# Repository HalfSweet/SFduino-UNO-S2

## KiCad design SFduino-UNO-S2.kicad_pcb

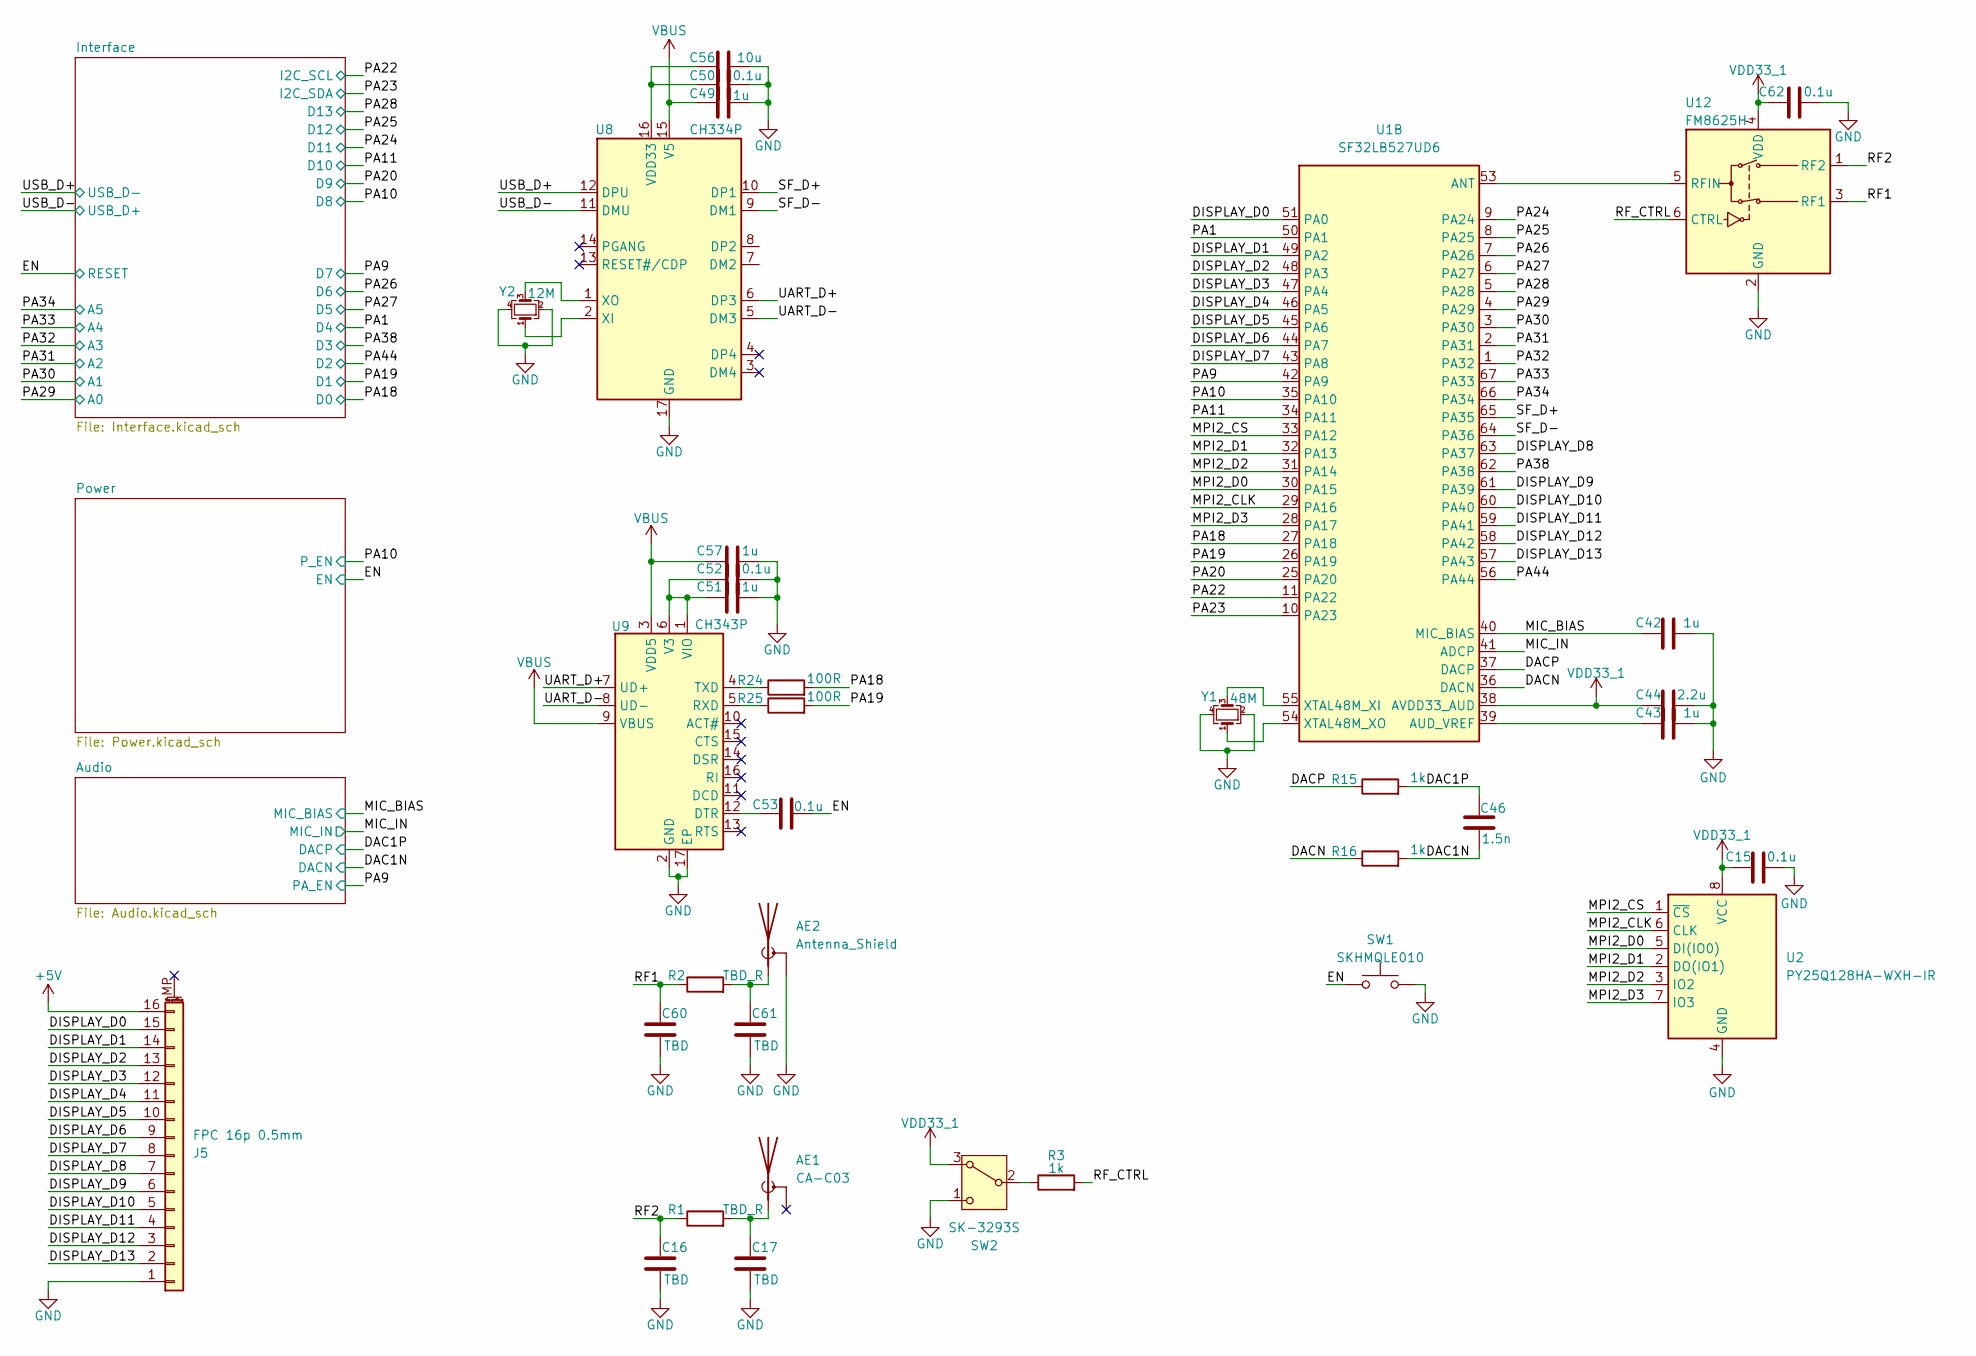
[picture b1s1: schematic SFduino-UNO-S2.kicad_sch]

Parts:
AE1: CA-C03
AE2: Antenna_Shield; U.FL_Molex_MCRF_73412-0110_Vertical
C15, C50, C52, C53, C62: 0.1u; C_0402_1005Metric
C16, C17, C60, C61: TBD; C_0402_1005Metric
C42, C43, C49, C51, C57: 1u; C_0402_1005Metric
C44: 2.2u; C_0402_1005Metric
C46: 1.5n; C_0402_1005Metric
C56: 10u; C_0402_1005Metric
J5: FPC 16p 0.5mm; Hirose_FH12-16S-0.5SH_1x16-1MP_P0.50mm_Horizontal
R1, R2: TBD_R; R_0402_1005Metric
R3, R15, R16: 1k; R_0402_1005Metric
R24, R25: 100R; R_0402_1005Metric
SW1: SKHMQLE010; KEY-SMD_4P-L6.2-W6.5-P4.50-LS8.0_SKHMXX
SW2: SK-3293S; SW-SMD_SK-3293S_mini_7P
U1: SF32LB527UD6; ArtInChip_QFN-68-1EP_7x7mm_P0.35mm_EP5.49x5.49mm
U2: PY25Q128HA-WXH-IR; WSON-8-1EP_6x5mm_P1.27mm_EP3.4x4.3mm
U8: CH334P; QFN-16-1EP_3x3mm_P0.5mm_EP1.7x1.7mm
U9: CH343P; QFN-16-1EP_3x3mm_P0.5mm_EP1.7x1.7mm
U12: FM8625H; Infineon_PG-TSNP-6-10_0.7x1.1mm_0.7x1.1mm_P0.4mm
Y1: 48M; Crystal_SMD_2016-4Pin_2.0x1.6mm
Y2: 12M; Crystal_SMD_2520-4Pin_2.5x2.0mm

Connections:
+5V: J5.16; also elsewhere on the board
/DAC1N: C46.2, R16.2; also elsewhere on the board
/DAC1P: C46.1, R15.2; also elsewhere on the board
/DACN: R16.1, U1.36 (DACN)
/DACP: R15.1, U1.37 (DACP)
/DISPLAY_D0: J5.15, U1.51 (PA0)
/DISPLAY_D1: J5.14, U1.49 (PA2)
/DISPLAY_D2: J5.13, U1.48 (PA3)
/DISPLAY_D3: J5.12, U1.47 (PA4)
/DISPLAY_D4: J5.11, U1.46 (PA5)
/DISPLAY_D5: J5.10, U1.45 (PA6)
/DISPLAY_D6: J5.9, U1.44 (PA7)
/DISPLAY_D7: J5.8, U1.43 (PA8)
/DISPLAY_D8: J5.7, U1.63 (PA37)
/DISPLAY_D9: J5.6, U1.61 (PA39)
/DISPLAY_D10: J5.5, U1.60 (PA40)
/DISPLAY_D11: J5.4, U1.59 (PA41)
/DISPLAY_D12: J5.3, U1.58 (PA42)
/DISPLAY_D13: J5.2, U1.57 (PA43)
/EN: C53.2, SW1.1; also elsewhere on the board
/MIC_BIAS: C42.1, U1.40 (MIC_BIAS); also elsewhere on the board
/MIC_IN: U1.41 (ADCP); also elsewhere on the board
/MPI2_CLK: U1.29 (PA16), U2.6 (CLK)
/MPI2_CS: U1.33 (PA12), U2.1 (~CS)
/MPI2_D0: U1.30 (PA15), U2.5 (DI(IO0))
/MPI2_D1: U1.32 (PA13), U2.2 (DO(IO1))
/MPI2_D2: U1.31 (PA14), U2.3 (IO2)
/MPI2_D3: U1.28 (PA17), U2.7 (IO3)
/PA1: U1.50 (PA1); also elsewhere on the board
/PA9: U1.42 (PA9); also elsewhere on the board
/PA10: U1.35 (PA10); also elsewhere on the board
/PA11: U1.34 (PA11); also elsewhere on the board
/PA18: R24.2, U1.27 (PA18); also elsewhere on the board
/PA19: R25.2, U1.26 (PA19); also elsewhere on the board
/PA20: U1.25 (PA20); also elsewhere on the board
/PA22: U1.11 (PA22); also elsewhere on the board
/PA23: U1.10 (PA23); also elsewhere on the board
/PA24: U1.9 (PA24); also elsewhere on the board
/PA25: U1.8 (PA25); also elsewhere on the board
/PA26: U1.7 (PA26); also elsewhere on the board
/PA27: U1.6 (PA27); also elsewhere on the board
/PA28: U1.5 (PA28); also elsewhere on the board
/PA29: U1.4 (PA29); also elsewhere on the board
/PA30: U1.3 (PA30); also elsewhere on the board
/PA31: U1.2 (PA31); also elsewhere on the board
/PA32: U1.1 (PA32); also elsewhere on the board
/PA33: U1.67 (PA33); also elsewhere on the board
/PA34: U1.66 (PA34); also elsewhere on the board
/PA38: U1.62 (PA38); also elsewhere on the board
/PA44: U1.56 (PA44); also elsewhere on the board
/RF1: C60.1, R2.1, U12.3 (RF1)
/RF2: C16.1, R1.1, U12.1 (RF2)
/RF_CTRL: R3.2, U12.6 (CTRL)
/SF_D+: U1.65 (PA35), U8.10 (DP1)
/SF_D-: U1.64 (PA36), U8.9 (DM1)
/UART_D+: U8.6 (DP3), U9.7 (UD+)
/UART_D-: U8.5 (DM3), U9.8 (UD-)
/USB_D+: U8.12 (DPU); also elsewhere on the board
/USB_D-: U8.11 (DMU); also elsewhere on the board
GND: AE2.2 (Shield), C15.2, C16.2, C17.2, C42.2, C43.2, C44.2, C49.2, C50.2, C51.2, C52.2, C56.2, C57.2, C60.2, C61.2, C62.2, J5.1, SW1.2, SW2.1 (C), U2.4 (GND), U8.17 (GND), U9.2 (GND), U9.17 (EP), U12.2 (GND), Y1.2, Y1.4, Y2.2, Y2.4; also elsewhere on the board
unnamed: AE1.1 (A), C17.1, R1.2
unnamed: AE2.1 (A), C61.1, R2.2
unnamed: R3.1, SW2.2 (B)
unnamed: C43.1, U1.39 (AUD_VREF)
unnamed: U1.55 (XTAL48M_XI), Y1.3
unnamed: U1.54 (XTAL48M_XO), Y1.1
unnamed: C50.1, C56.1, U8.16 (VDD33)
unnamed: U8.2 (XI), Y2.1
unnamed: U8.1 (XO), Y2.3
unnamed: C53.1, U9.12 (DTR)
unnamed: R25.1, U9.5 (RXD)
unnamed: R24.1, U9.4 (TXD)
unnamed: C51.1, C52.1, U9.1 (VIO), U9.6 (V3)
unnamed: U1.53 (ANT), U12.5 (RFIN)
VBUS: C49.1, C57.1, U8.15 (V5), U9.3 (VDD5), U9.9 (VBUS); also elsewhere on the board
VDD33_1: C15.1, C44.1, C62.1, SW2.3 (A), U1.38 (AVDD33_AUD), U2.8 (VCC), U12.4 (VDD); also elsewhere on the board

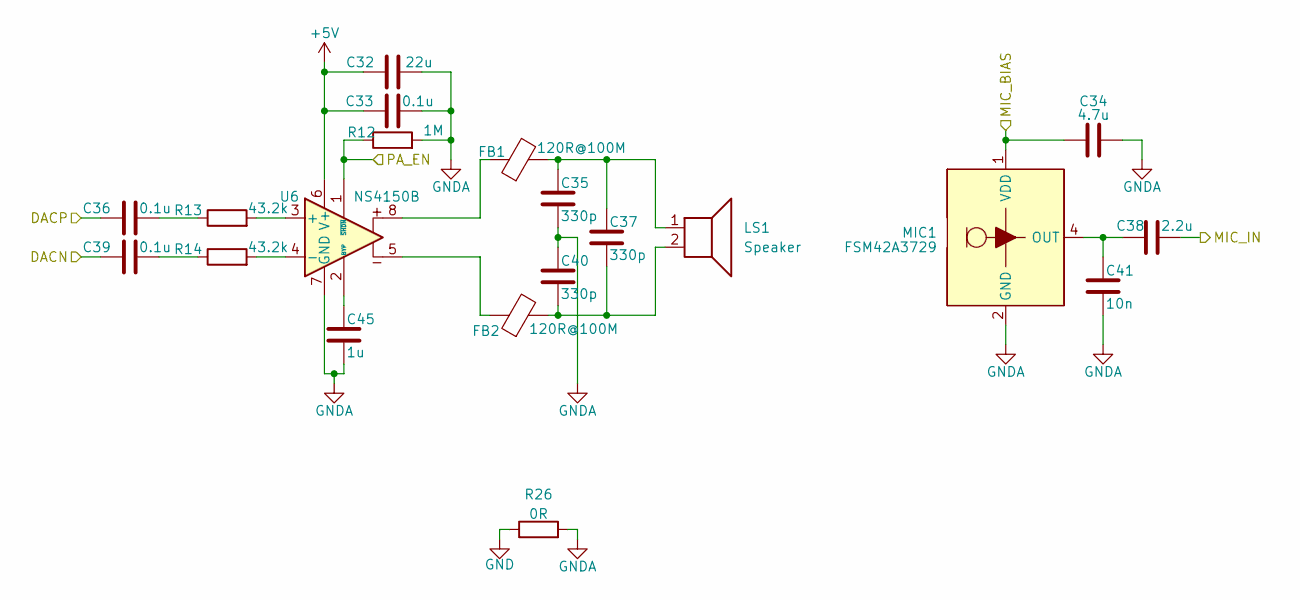
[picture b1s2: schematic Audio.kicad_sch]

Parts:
C32: 22u; C_0603_1608Metric
C33, C36, C39: 0.1u; C_0402_1005Metric
C34: 4.7u; C_0402_1005Metric
C35, C37, C40: 330p; C_0402_1005Metric
C38: 2.2u; C_0402_1005Metric
C41: 10n; C_0402_1005Metric
C45: 1u; C_0402_1005Metric
FB1, FB2: 120R@100M; L_0402_1005Metric
LS1: Speaker; FUET-1818-1.8x1.8mm-H6.1mm
MIC1: FSM42A3729; MIC-SMD_4P-L3.8-W3.0
R12: 1M; R_0402_1005Metric
R13, R14: 43.2k; R_0402_1005Metric
R26: 0R; R_0603_1608Metric
U6: NS4150B; MSOP-8_3x3mm_P0.65mm

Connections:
+5V: C32.1, C33.1, U6.6 (V+); also elsewhere on the board
/DAC1N: C39.1; also elsewhere on the board
/DAC1P: C36.1; also elsewhere on the board
/MIC_BIAS: C34.1, MIC1.1 (VDD); also elsewhere on the board
/MIC_IN: C38.2; also elsewhere on the board
/PA9: R12.1, U6.1 (~SHDN); also elsewhere on the board
GND: R26.1; also elsewhere on the board
GNDA: C32.2, C33.2, C34.2, C35.2, C40.1, C41.2, C45.2, MIC1.2 (GND), MIC1.3 (GND), R12.2, R26.2, U6.7 (GND)
unnamed: C35.1, C37.1, FB1.2, LS1.1
unnamed: C36.2, R13.1
unnamed: C37.2, C40.2, FB2.2, LS1.2
unnamed: C39.2, R14.1
unnamed: FB1.1, U6.8
unnamed: FB2.1, U6.5
unnamed: C38.1, C41.1, MIC1.4 (OUT)
unnamed: R13.2, U6.3 (+)
unnamed: R14.2, U6.4 (-)
unnamed: C45.1, U6.2 (BYP)

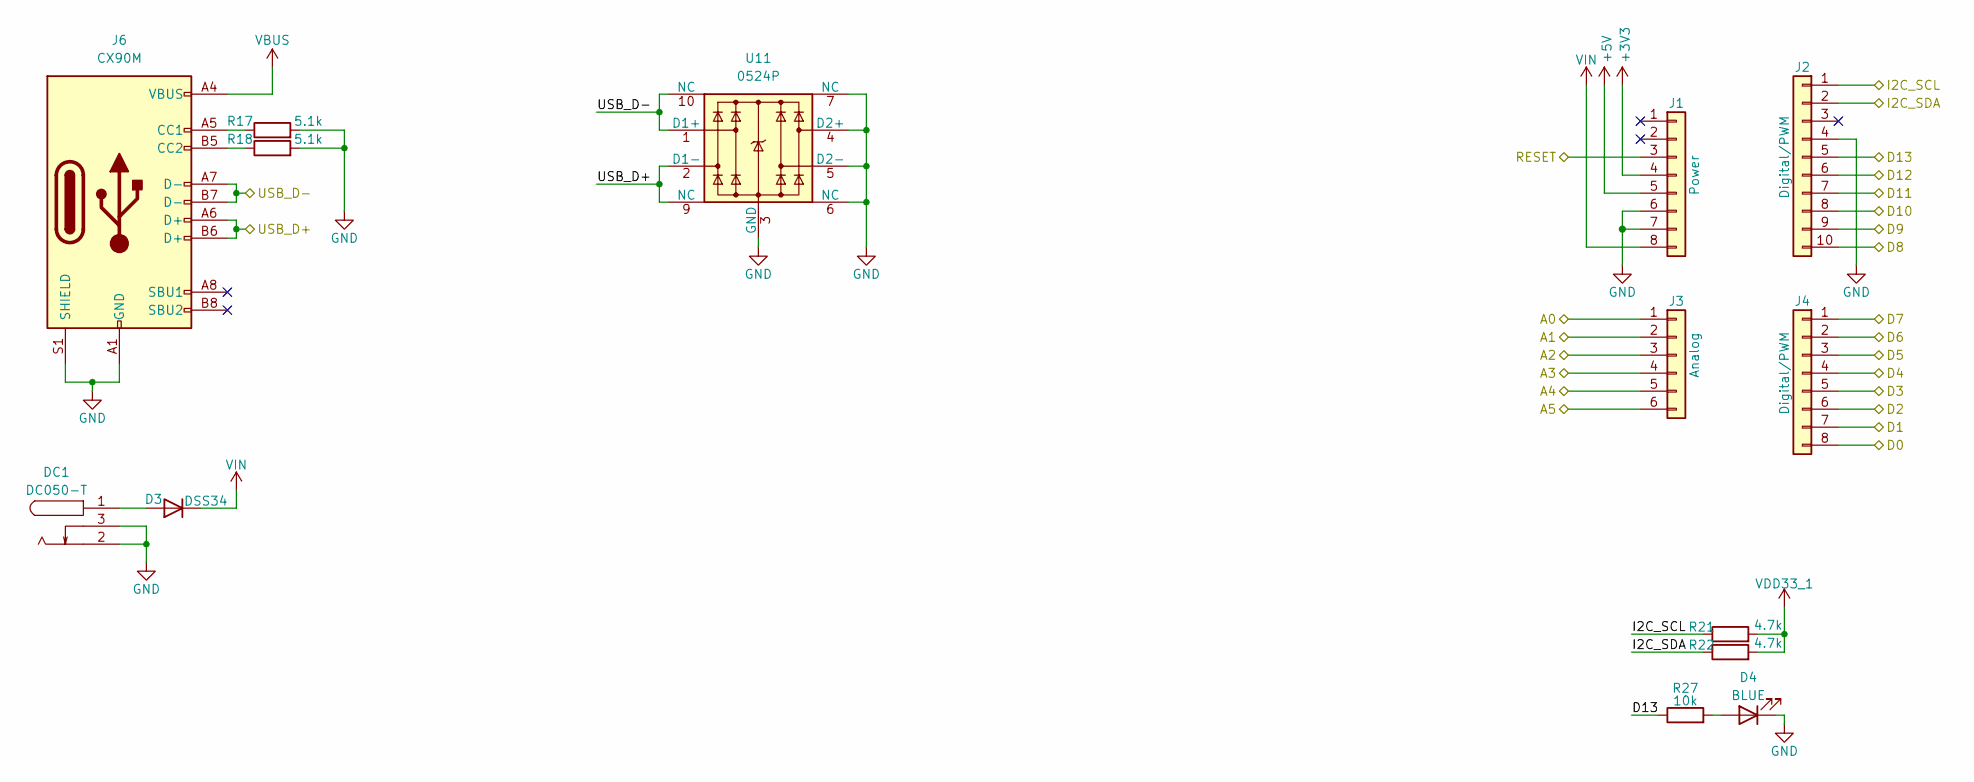
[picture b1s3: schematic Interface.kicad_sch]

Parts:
D3: DSS34; D_SOD-123F; LCSC C511866
D4: BLUE; LED_0603_1608Metric
DC1: DC050-T; BarrelJack_GCT_DCJ200-10-A_Horizontal
J1: Power; PinSocket_1x08_P2.54mm_Vertical
J2: Digital/PWM; PinSocket_1x10_P2.54mm_Vertical
J3: Analog; PinSocket_1x06_P2.54mm_Vertical
J4: Digital/PWM; PinSocket_1x08_P2.54mm_Vertical
J6: CX90M; USB-C-SMD_CX90M-16P
R17, R18: 5.1k; R_0402_1005Metric
R21, R22: 4.7k; R_0402_1005Metric
R27: 10k; R_0402_1005Metric
U11: 0524P; USON-10_2.5x1.0mm_P0.5mm

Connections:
+3V3: J1.4; also elsewhere on the board
+5V: J1.5; also elsewhere on the board
/EN: J1.3; also elsewhere on the board
/PA1: J4.4; also elsewhere on the board
/PA9: J4.1; also elsewhere on the board
/PA10: J2.10; also elsewhere on the board
/PA11: J2.8; also elsewhere on the board
/PA18: J4.8; also elsewhere on the board
/PA19: J4.7; also elsewhere on the board
/PA20: J2.9; also elsewhere on the board
/PA22: J2.1, R21.1; also elsewhere on the board
/PA23: J2.2, R22.1; also elsewhere on the board
/PA24: J2.7; also elsewhere on the board
/PA25: J2.6; also elsewhere on the board
/PA26: J4.2; also elsewhere on the board
/PA27: J4.3; also elsewhere on the board
/PA28: J2.5, R27.1; also elsewhere on the board
/PA29: J3.1; also elsewhere on the board
/PA30: J3.2; also elsewhere on the board
/PA31: J3.3; also elsewhere on the board
/PA32: J3.4; also elsewhere on the board
/PA33: J3.5; also elsewhere on the board
/PA34: J3.6; also elsewhere on the board
/PA38: J4.5; also elsewhere on the board
/PA44: J4.6; also elsewhere on the board
/USB_D+: J6.A7 (D-), J6.B7 (D-), U11.1 (D1+), U11.10 (NC); also elsewhere on the board
/USB_D-: J6.A6 (D+), J6.B6 (D+), U11.2 (D1-), U11.9 (NC); also elsewhere on the board
GND: D4.1 (K), DC1.2, DC1.3, J1.6, J1.7, J2.4, J6.A1 (GND), J6.A12 (GND), J6.B1 (GND), J6.B12 (GND), J6.S1 (SHIELD), R17.2, R18.2, U11.3 (GND), U11.4 (D2+), U11.5 (D2-), U11.6 (NC), U11.7 (NC), U11.8 (GND); also elsewhere on the board
unnamed: D3.2 (A), DC1.1
unnamed: D4.2 (A), R27.2
unnamed: J6.A5 (CC1), R17.1
unnamed: J6.B5 (CC2), R18.1
VBUS: J6.A4 (VBUS), J6.A9 (VBUS), J6.B4 (VBUS), J6.B9 (VBUS); also elsewhere on the board
VDD33_1: R21.2, R22.2; also elsewhere on the board
VIN: D3.1 (K), J1.8; also elsewhere on the board

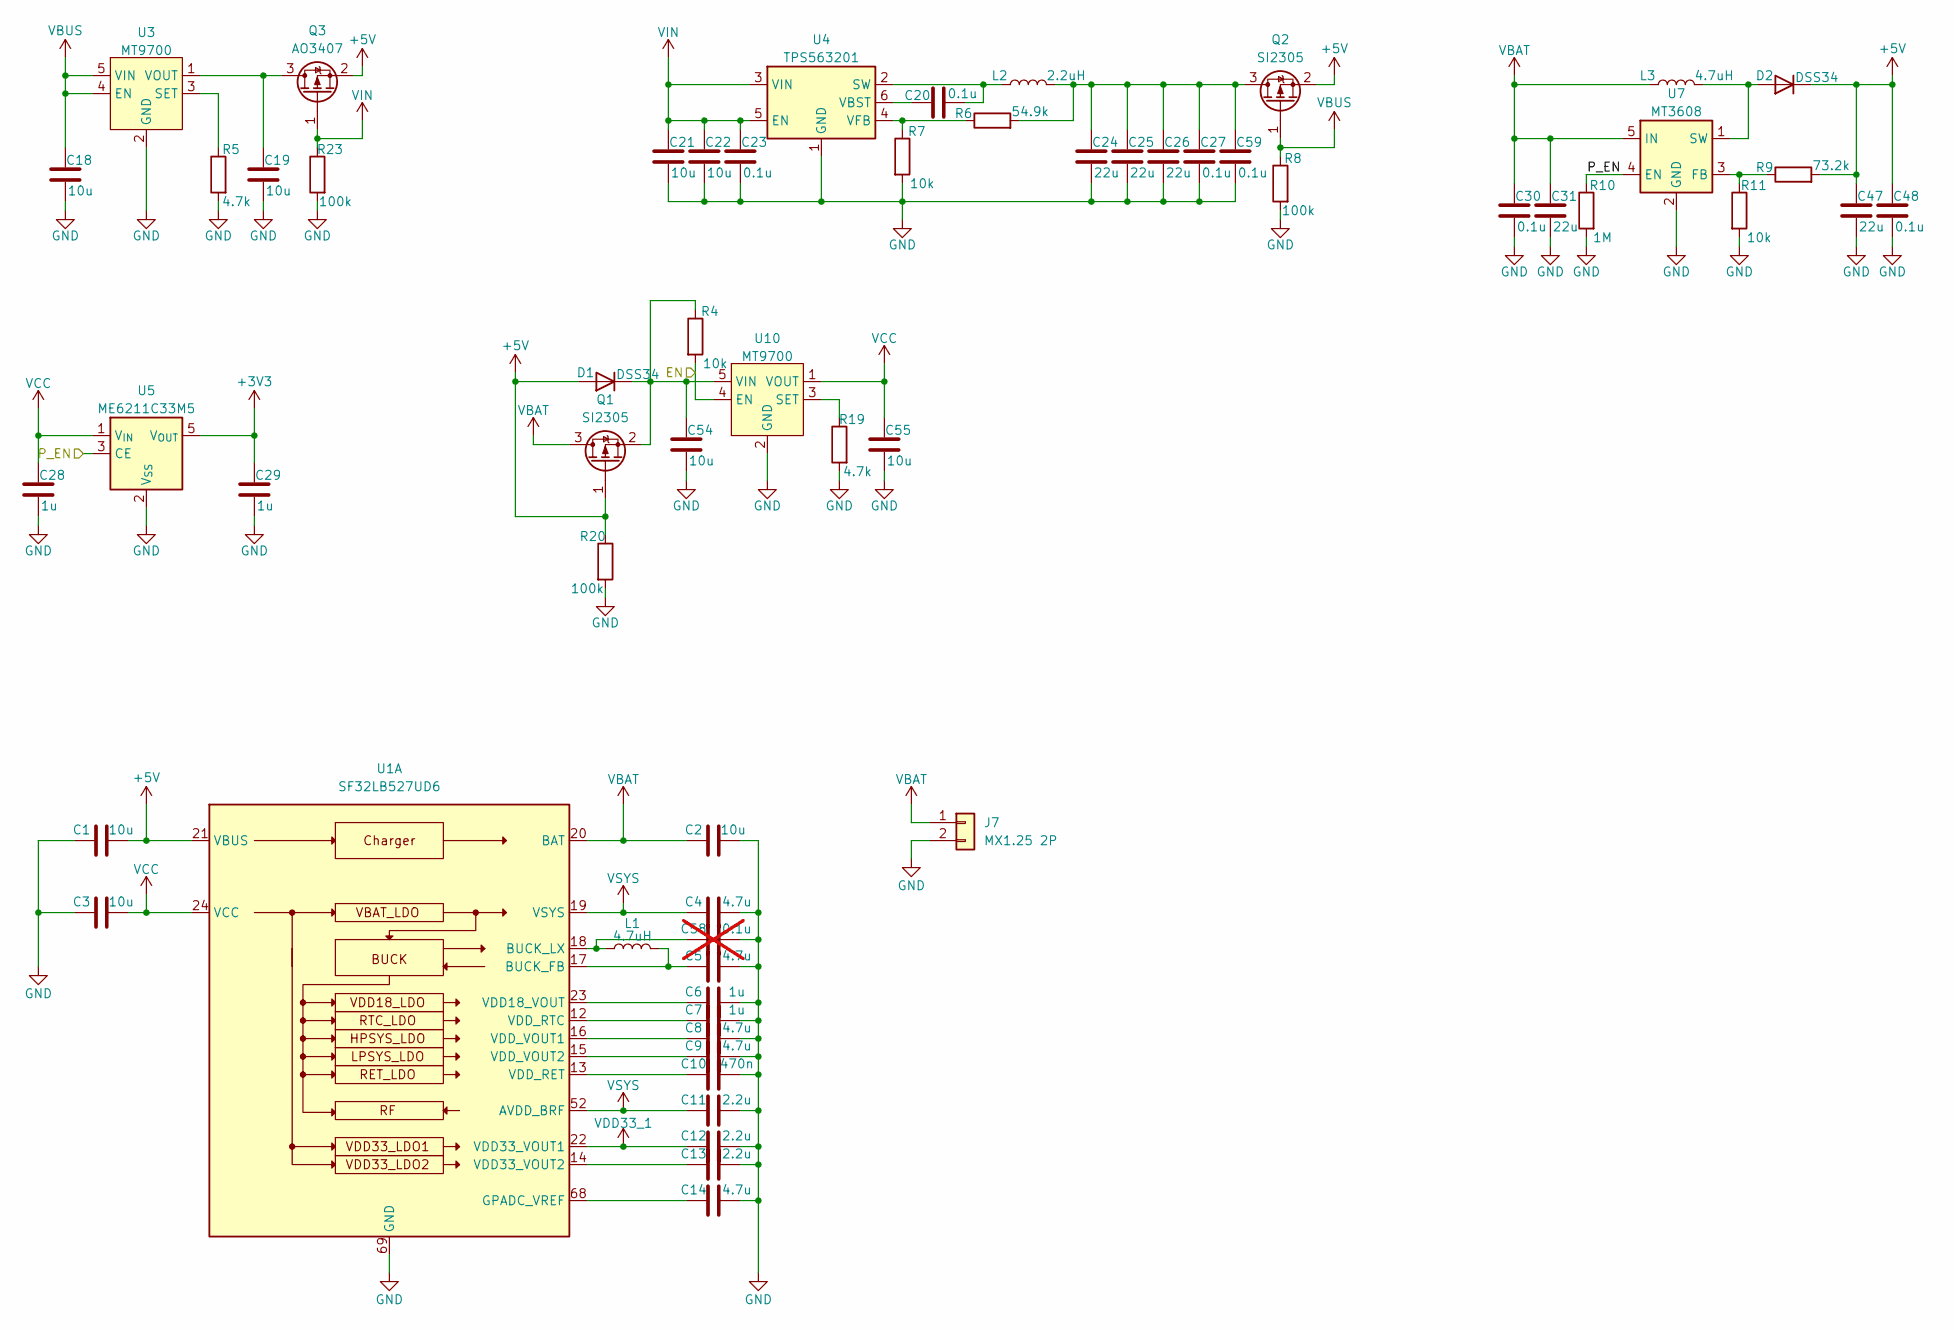
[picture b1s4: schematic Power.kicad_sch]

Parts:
C1, C2, C3, C18, C19, C54, C55: 10u; C_0402_1005Metric
C4, C5, C8, C9, C14: 4.7u; C_0402_1005Metric
C6, C7, C28, C29: 1u; C_0402_1005Metric
C10: 470n; C_0402_1005Metric
C11, C12, C13: 2.2u; C_0402_1005Metric
C20, C23, C27, C30, C48, C59: 0.1u; C_0402_1005Metric
C21, C22: 10u; C_0603_1608Metric
C24, C25, C26, C31, C47: 22u; C_0603_1608Metric
C58: 0.1u; C_0402_1005Metric; not fitted
D1, D2: DSS34; D_SOD-123F; LCSC C511866
J7: MX1.25 2P; JST_GH_SM02B-GHS-TB_1x02-1MP_P1.25mm_Horizontal
L1: 4.7uH; L_Murata_DFE201610P
L2: 2.2uH; L_Sunlord_SWPA4020S
L3: 4.7uH; L_Sunlord_SWPA4020S
Q1, Q2: SI2305; SOT-23
Q3: AO3407; SOT-23
R4, R7, R11: 10k; R_0402_1005Metric
R5, R19: 4.7k; R_0402_1005Metric
R6: 54.9k; R_0402_1005Metric
R8, R20, R23: 100k; R_0402_1005Metric
R9: 73.2k; R_0402_1005Metric
R10: 1M; R_0402_1005Metric
U1: SF32LB527UD6; ArtInChip_QFN-68-1EP_7x7mm_P0.35mm_EP5.49x5.49mm
U3, U10: MT9700; SOT-23-5
U4: TPS563201; SOT-23-6
U5: ME6211C33M5; SOT-23-5
U7: MT3608; SOT-23-6

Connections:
+3V3: C29.1, U5.5 (V_{OUT}); also elsewhere on the board
+5V: C1.2, C47.1, C48.1, D1.2 (A), D2.1 (K), Q1.1 (G), Q2.2 (S), Q3.2 (S), R9.2, R20.1, U1.21 (VBUS); also elsewhere on the board
/EN: R4.2, U10.4 (EN); also elsewhere on the board
/PA10: R10.1, U5.3 (CE), U7.4 (EN); also elsewhere on the board
GND: C1.1, C2.2, C3.1, C4.2, C5.2, C6.2, C7.2, C8.2, C9.2, C10.2, C11.2, C12.2, C13.2, C14.2, C18.2, C19.2, C21.2, C22.2, C23.2, C24.2, C25.2, C26.2, C27.2, C28.2, C29.2, C30.2, C31.2, C47.2, C48.2, C54.2, C55.2, C58.2, C59.2, J7.2, R5.2, R7.2, R8.2, R10.2, R11.2, R19.2, R20.2, R23.2, U1.69 (GND), U3.2 (GND), U4.1 (GND), U5.2 (V_{SS}), U7.2 (GND), U10.2 (GND); also elsewhere on the board
unnamed: C54.1, D1.1 (K), Q1.2 (S), R4.1, U10.5 (VIN)
unnamed: D2.2 (A), L3.2, U7.1 (SW)
unnamed: C24.1, C25.1, C26.1, C27.1, C59.1, L2.2, Q2.3 (D), R6.2
unnamed: C19.1, Q3.3 (D), U3.1 (VOUT)
unnamed: C5.1, L1.2, U1.17 (BUCK_FB)
unnamed: C58.1, L1.1, U1.18 (BUCK_LX)
unnamed: C14.1, U1.68 (GPADC_VREF)
unnamed: C6.1, U1.23 (VDD18_VOUT)
unnamed: C13.1, U1.14 (VDD33_VOUT2)
unnamed: C10.1, U1.13 (VDD_RET)
unnamed: C7.1, U1.12 (VDD_RTC)
unnamed: C8.1, U1.16 (VDD_VOUT1)
unnamed: C9.1, U1.15 (VDD_VOUT2)
unnamed: R5.1, U3.3 (SET)
unnamed: C20.2, L2.1, U4.2 (SW)
unnamed: C20.1, U4.6 (VBST)
unnamed: R6.1, R7.1, U4.4 (VFB)
unnamed: R9.1, R11.1, U7.3 (FB)
unnamed: R19.1, U10.3 (SET)
VBAT: C2.1, C30.1, C31.1, J7.1, L3.1, Q1.3 (D), U1.20 (BAT), U7.5 (IN)
VBUS: C18.1, Q2.1 (G), R8.1, U3.4 (EN), U3.5 (VIN); also elsewhere on the board
VCC: C3.2, C28.1, C55.1, U1.24 (VCC), U5.1 (V_{IN}), U10.1 (VOUT)
VDD33_1: C12.1, U1.22 (VDD33_VOUT1); also elsewhere on the board
VIN: C21.1, C22.1, C23.1, Q3.1 (G), R23.1, U4.3 (VIN), U4.5 (EN); also elsewhere on the board
VSYS: C4.1, C11.1, U1.19 (VSYS), U1.52 (AVDD_BRF)

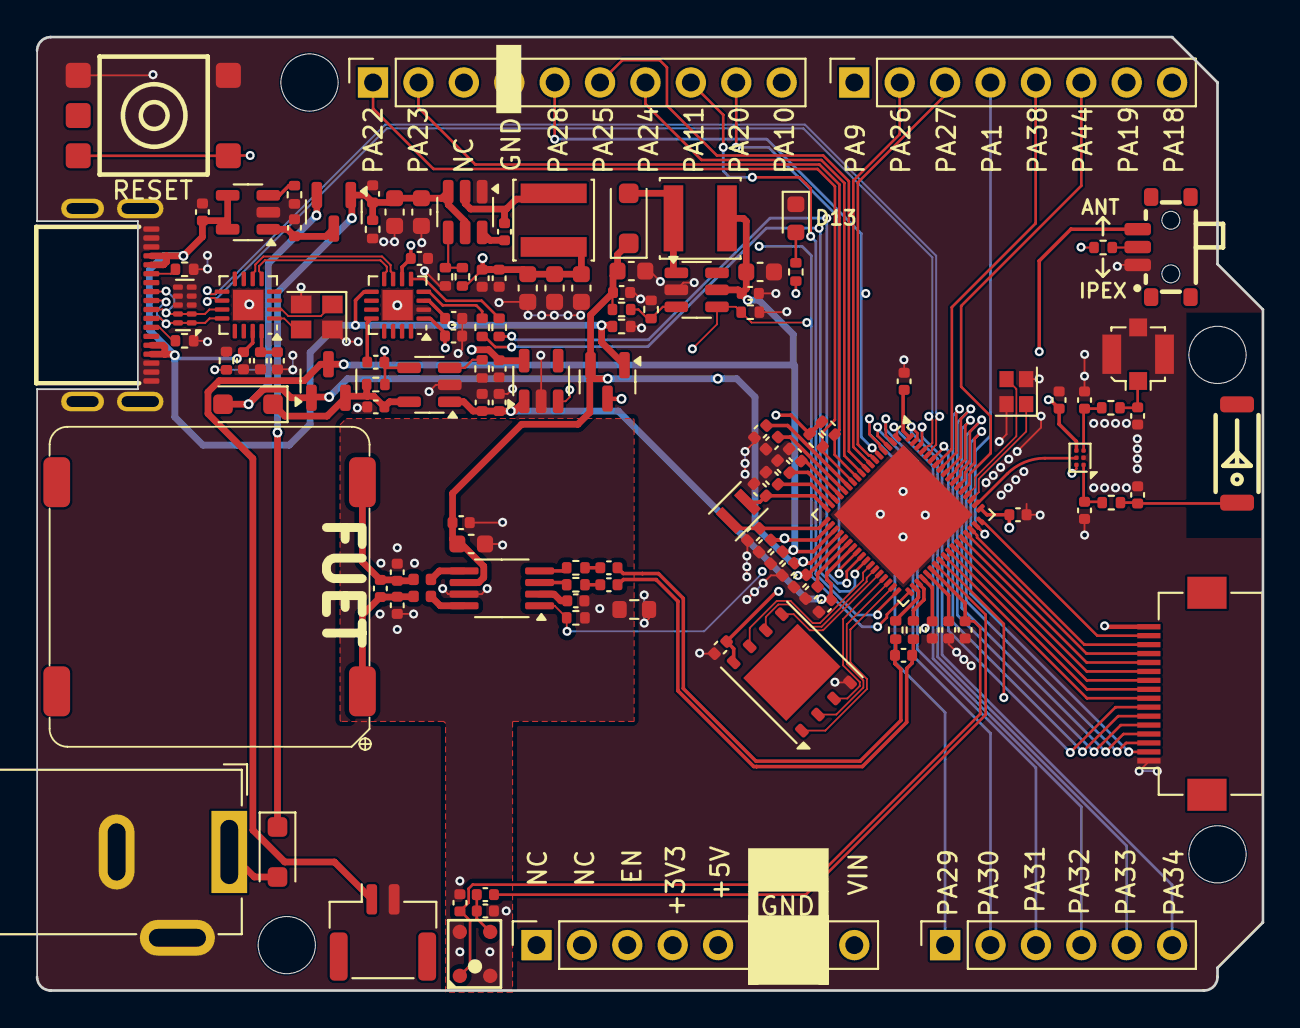
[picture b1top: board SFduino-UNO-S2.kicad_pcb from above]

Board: 4 copper layers, 68.6 x 53.3 mm, 133 parts (0 on the bottom side), 115 nets.

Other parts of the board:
MH1, MH2, MH3, MH4: MountingHole_3.2mm

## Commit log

2024-12-08 update: 添加原理图
2024-12-08 fix: 修复电源架构
2024-12-10 update: 更新PCB
2024-12-15 update:
